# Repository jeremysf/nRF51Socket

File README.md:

# nRF51Socket
QFN48 socket to J-Link/JTAG 20-pin connector to program bootloaders, etc for Nordic nRF51.

I included a USB connector as an alternative to using the 5V power from the J-Link, but haven't had to use that yet, the power from the J-Link device works great!

I also included a 16mhz crystal in the design so that I could boot up the nRF51 and do some basic validation. Probably could get away without populating those or related components.

The socket is available on Amazon.com and Ebay.com for about $100 it's a QFN-48(52)BT-0.4-01 manufactured by Enplas.

![alt text]
(https://pbs.twimg.com/media/CR9HupoUYAArvvp.jpg)

![alt text]
(https://pbs.twimg.com/media/CR9HuqqVAAADbZV.jpg)

![alt text]
(https://pbs.twimg.com/media/CR9HuqIVAAAAnUr.jpg)

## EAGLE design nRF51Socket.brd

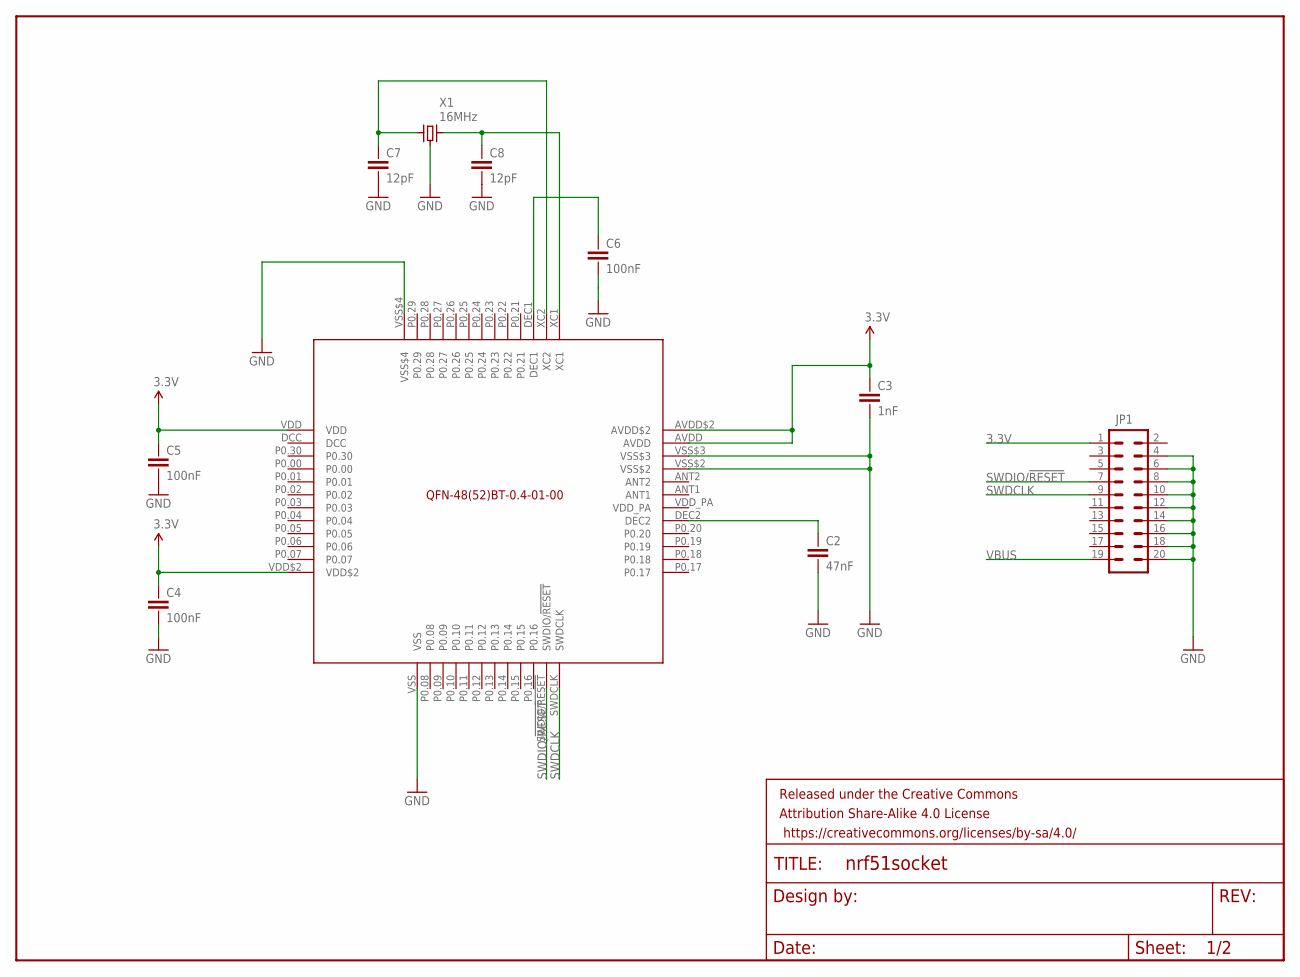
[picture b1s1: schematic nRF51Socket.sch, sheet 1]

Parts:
C2: 47nF; CAP-403
C3: 1nF; CAP-403
C4, C5, C6: 100nF; CAP-403
C7, C8: 12pF; CAP-403
FRAME1: FRAME-LETTERNO_PACKAGE; DUMMY
JP1: M10X2; 2X10
U1: QFN-48(52)BT-0.4-01-00
X1: 16MHz; CRYSTAL-2520

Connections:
3.3V: C3.2 (1), C4.2 (1), C5.2 (1), JP1.1, U1.AVDD, U1.AVDD$2, U1.VDD, U1.VDD$2; also elsewhere on the board
GND: C2.1 (2), C3.1 (2), C4.1 (2), C5.1 (2), C6.1 (2), C7.1 (2), C8.1 (2), JP1.4, JP1.6, JP1.8, JP1.10, JP1.12, JP1.14, JP1.16, JP1.18, JP1.20, U1.VSS, U1.VSS$2, U1.VSS$3, U1.VSS$4, X1.GND@1 (GND), X1.GND@2 (GND); also elsewhere on the board
unnamed: C2.2 (1), U1.DEC2
unnamed: C6.2 (1), U1.DEC1
unnamed: C8.2 (1), U1.XC1, X1.3
unnamed: C7.2 (1), U1.XC2, X1.1
SWDCLK: JP1.9, U1.SWDCLK
SWDIO/!RESET: JP1.7, U1.SWDIO/!RESET
VBUS: JP1.19; also elsewhere on the board

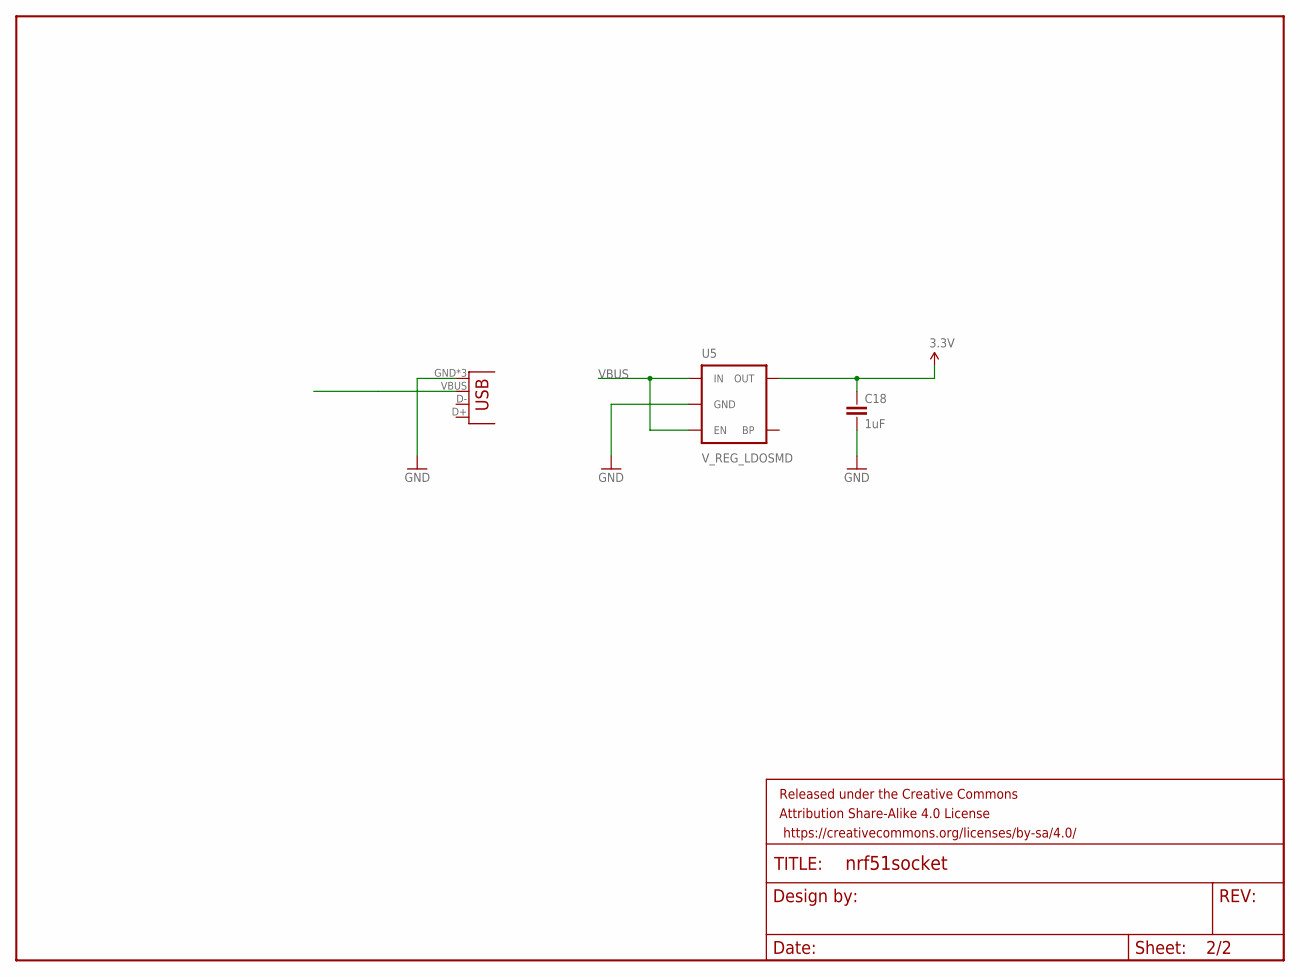
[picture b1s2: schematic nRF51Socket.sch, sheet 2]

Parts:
C18: 1uF; CAP-403
FRAME2: FRAME-LETTERNO_PACKAGE; DUMMY
JP2: USB-MICROB
U5: V_REG_LDOSMD; SOT23-5

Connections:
3.3V: C18.2 (1), U5.5 (OUT); also elsewhere on the board
GND: C18.1 (2), JP2.GND, JP2.MT1 (GND), JP2.MT2 (GND), U5.2 (GND); also elsewhere on the board
VBUS: JP2.VBUS, U5.1 (IN), U5.3 (EN); also elsewhere on the board

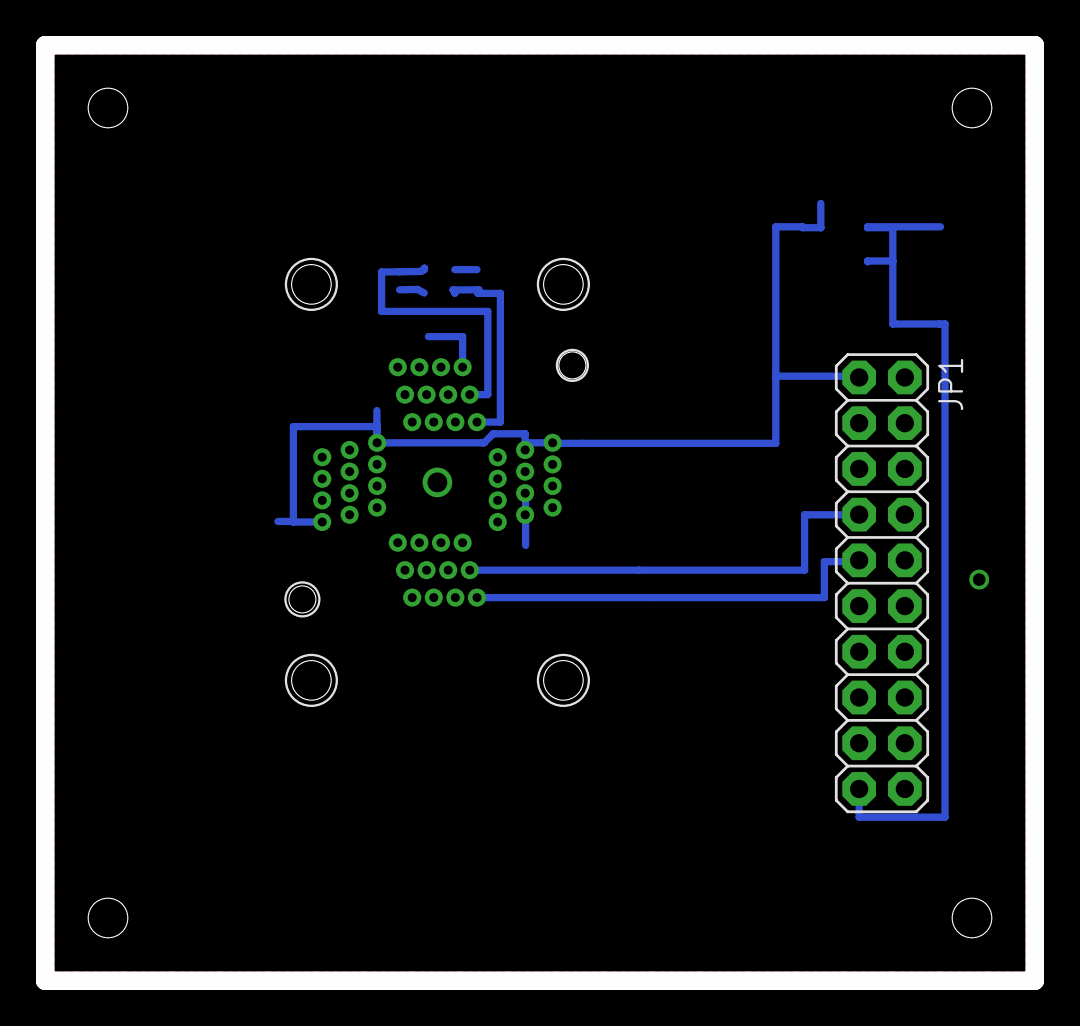
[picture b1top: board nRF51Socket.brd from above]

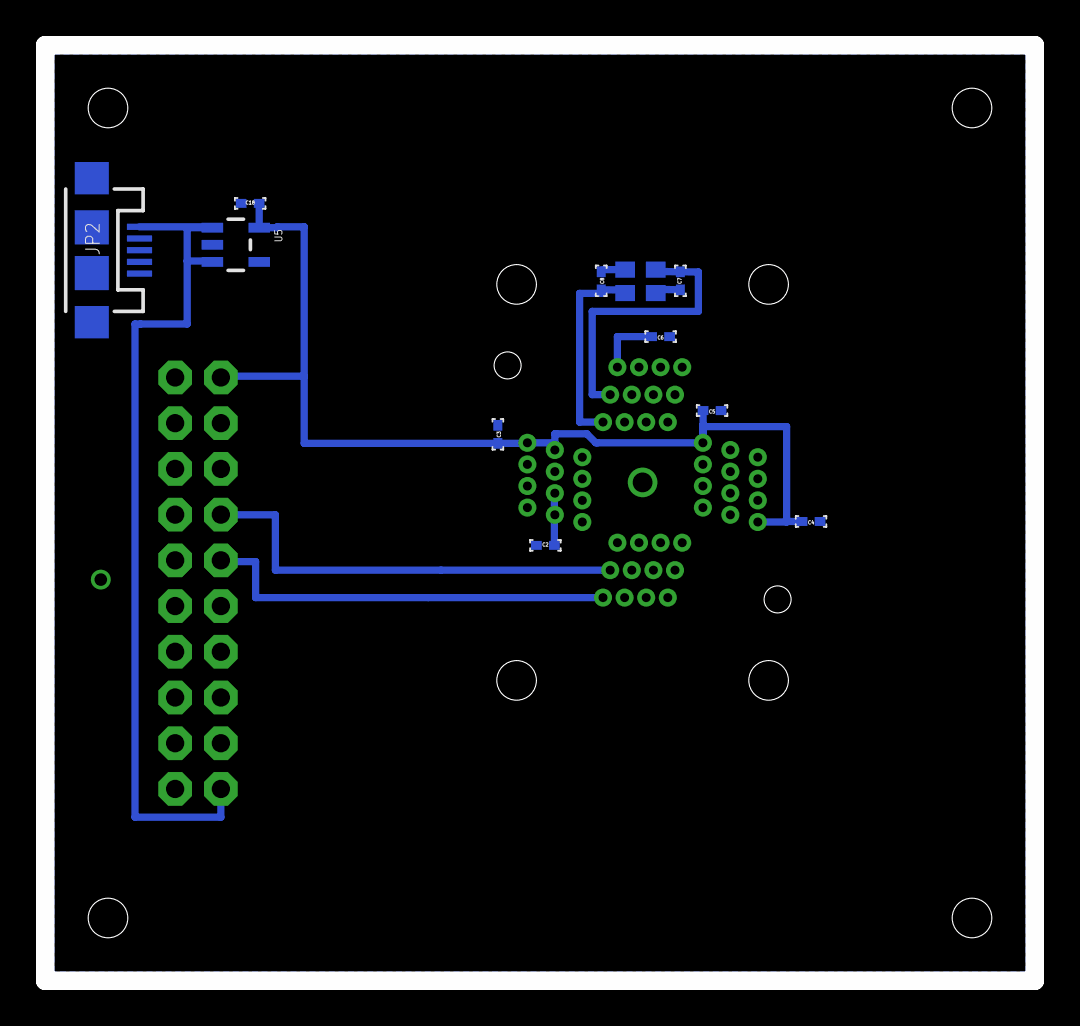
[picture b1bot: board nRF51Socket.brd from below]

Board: 2 copper layers, 55.0 x 52.0 mm, 15 parts (11 on the bottom side), 9 nets.

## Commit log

2015-10-21 Initial commit.
2015-10-21 First revison.
2015-10-22 Changed to 20pin jtag socket.
2015-10-25 More routable trace location.

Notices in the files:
parts and their libraries:
SparkFun-Aesthetics: Licensing: Creative Commons ShareAlike 4.0 International - https://creativecommons.org/licenses/by-sa/4.0
SparkFun-Aesthetics: Released under the Creative Commons Attribution Share-Alike 4.0 License
SparkFun-Aesthetics: https://creativecommons.org/licenses/by-sa/4.0
